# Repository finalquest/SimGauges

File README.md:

# SimGauges
XSIM simulator gauges control. Arduino PCB and arduino Code

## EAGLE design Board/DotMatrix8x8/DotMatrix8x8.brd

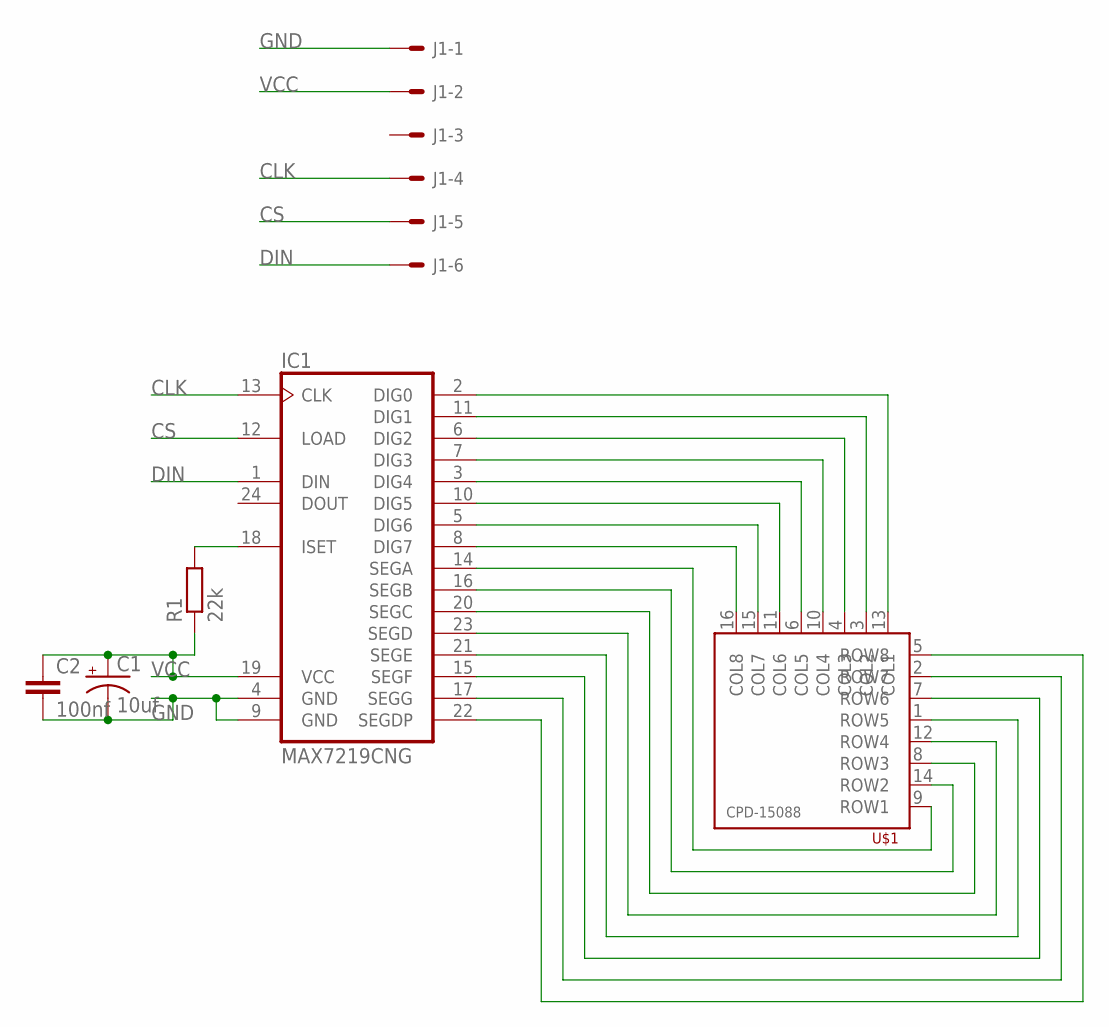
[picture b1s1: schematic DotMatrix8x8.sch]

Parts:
C1: 10uf; E2,5-6
C2: 100nf; C025-025X050
IC1: MAX7219CNG; DIL24-3
J1: 22-27-2061-06; 6410-06
R1: 22k; 0207/10
U$1: CPD-15088YGD2/A; CPD15088

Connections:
CLK: IC1.13 (CLK), J1.4
CS: IC1.12 (LOAD), J1.5
DIN: IC1.1 (DIN), J1.6
GND: C1.-, C2.2, IC1.4 (GND), IC1.9 (GND), J1.1
unnamed: IC1.18 (ISET), R1.2
unnamed: IC1.2 (DIG0), U$1.13 (COL1)
unnamed: IC1.11 (DIG1), U$1.3 (COL2)
unnamed: IC1.6 (DIG2), U$1.4 (COL3)
unnamed: IC1.7 (DIG3), U$1.10 (COL4)
unnamed: IC1.3 (DIG4), U$1.6 (COL5)
unnamed: IC1.10 (DIG5), U$1.11 (COL6)
unnamed: IC1.5 (DIG6), U$1.15 (COL7)
unnamed: IC1.8 (DIG7), U$1.16 (COL8)
unnamed: IC1.14 (SEGA), U$1.9 (ROW1)
unnamed: IC1.16 (SEGB), U$1.14 (ROW2)
unnamed: IC1.20 (SEGC), U$1.8 (ROW3)
unnamed: IC1.23 (SEGD), U$1.12 (ROW4)
unnamed: IC1.21 (SEGE), U$1.1 (ROW5)
unnamed: IC1.15 (SEGF), U$1.7 (ROW6)
unnamed: IC1.17 (SEGG), U$1.2 (ROW7)
unnamed: IC1.22 (SEGDP), U$1.5 (ROW8)
VCC: C1.+, C2.1, IC1.19 (VCC), J1.2, R1.1

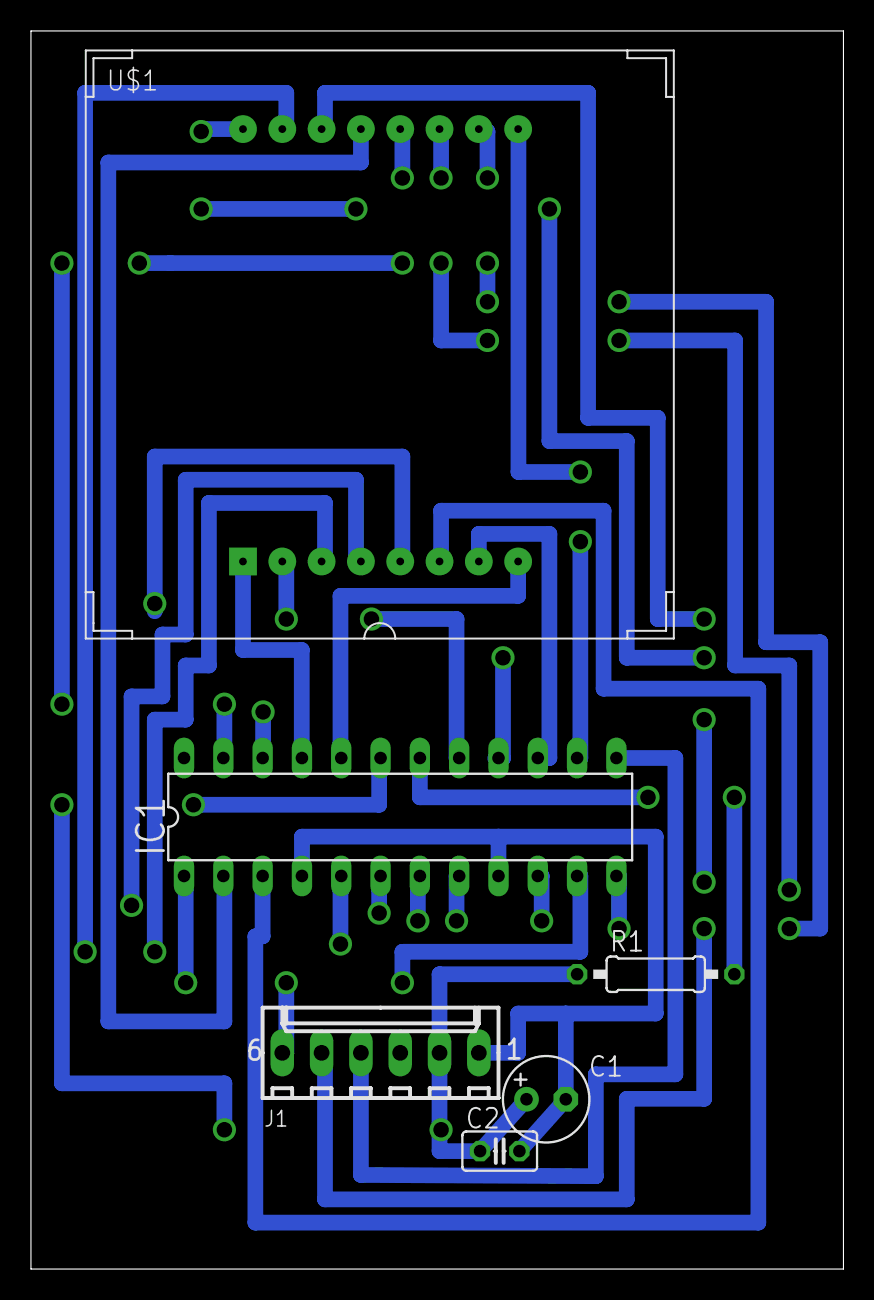
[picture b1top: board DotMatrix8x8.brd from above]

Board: 2 copper layers, 52.5 x 80.0 mm, 6 parts (0 on the bottom side), 22 nets.

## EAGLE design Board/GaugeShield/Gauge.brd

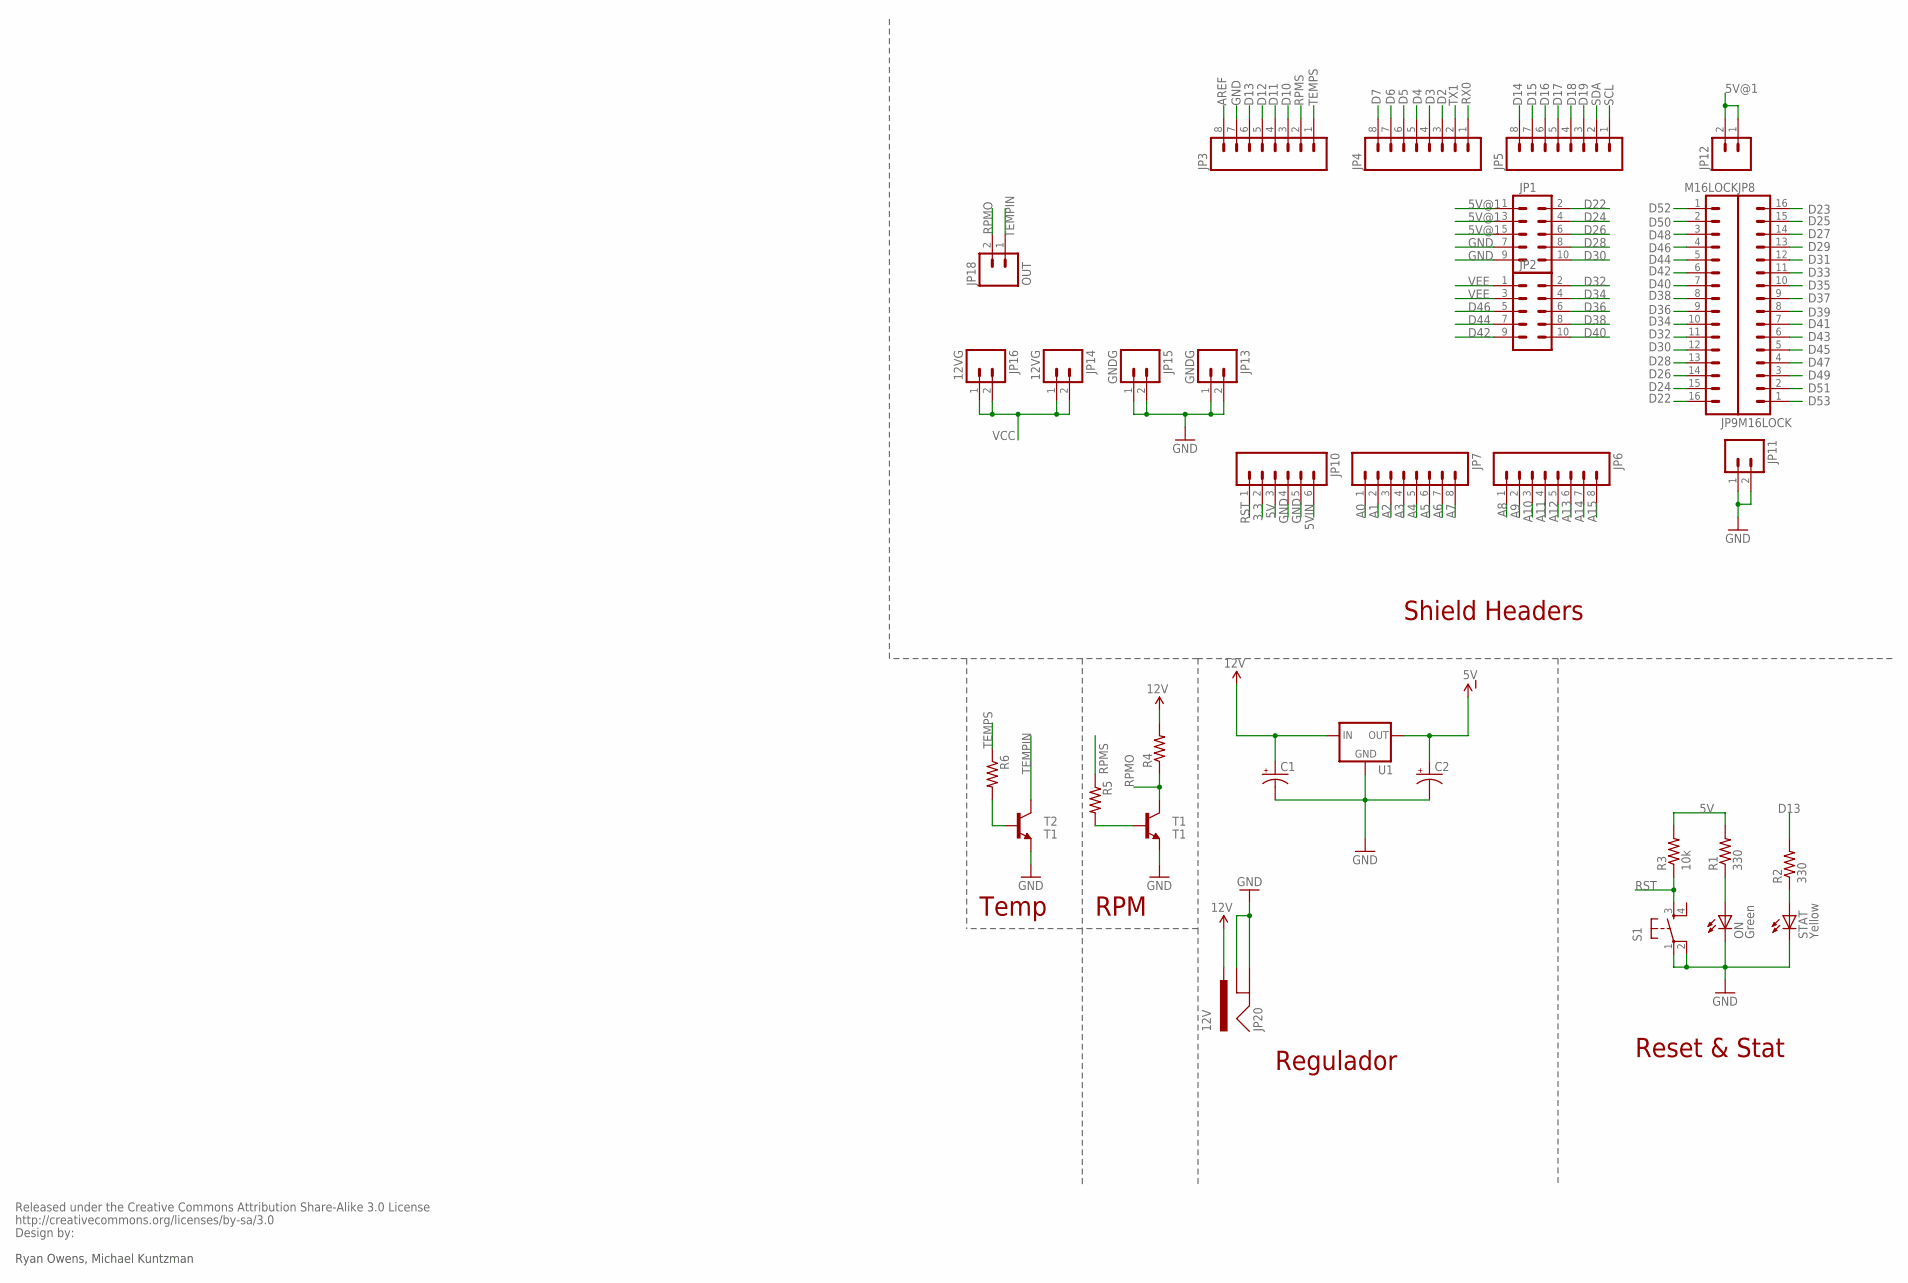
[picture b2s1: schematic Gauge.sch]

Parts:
C1, C2: 100UF-25V-20%(PTH); CPOL-RADIAL-100UF-25V
JP1, JP2: M05X2PTH; AVR_ICSP
JP3, JP4, JP5, JP6, JP7: M08LOCK; 1X08_LOCK
JP8, JP9: M16LOCK; 1X16_LOCK
JP10: M06LOCK; 1X06_LOCK
JP11, JP12: M02LOCK; 1X02_LOCK
JP13, JP15: GNDG; MOLEX-1X2
JP14, JP16: 12VG; MOLEX-1X2
JP18: OUT; MOLEX-1X2
JP20: 12V; POWER_JACK_PTH_LOCK
ON: Green; LED-0603
R1, R2: 330; 0603-RES
R3: 10k; 0603-RES
R4, R5, R6: RESISTORPTH-1/2W; AXIAL-0.5
S1: TAC_SWITCHSMD; TACTILE_SWITCH_SMD
STAT: Yellow; LED-0603
T1, T2: T1; TO-92
U1: V_REG_78XX-TO-220; TO-220-ALT
U$2: CREATIVE_COMMONS

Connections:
3.3: JP10.2
5V: JP10.3, R1.2, R3.2
5V@1: JP1.1, JP1.3, JP1.5, JP12.1, JP12.2
5VIN: C2.1 (+), JP10.6, U1.OUT
A0: JP7.1
A1: JP7.2
A2: JP7.3
A3: JP7.4
A4: JP7.5
A5: JP7.6
A6: JP7.7
A7: JP7.8
A8: JP6.1
A9: JP6.2
A10: JP6.3
A11: JP6.4
A12: JP6.5
A13: JP6.6
A14: JP6.7
A15: JP6.8
AREF: JP3.8
D2: JP4.3
D3: JP4.4
D4: JP4.5
D5: JP4.6
D6: JP4.7
D7: JP4.8
D10: JP3.3
D11: JP3.4
D12: JP3.5
D13: JP3.6, R2.2
D14: JP5.8
D15: JP5.7
D16: JP5.6
D17: JP5.5
D18: JP5.4
D19: JP5.3
D22: JP1.2, JP9.16
D23: JP8.16
D24: JP1.4, JP9.15
D25: JP8.15
D26: JP1.6, JP9.14
D27: JP8.14
D28: JP1.8, JP9.13
D29: JP8.13
D30: JP1.10, JP9.12
D31: JP8.12
D32: JP2.2, JP9.11
D33: JP8.11
D34: JP2.4, JP9.10
D35: JP8.10
D36: JP2.6, JP9.9
D37: JP8.9
D38: JP2.8, JP9.8
D39: JP8.8
D40: JP2.10, JP9.7
D41: JP8.7
D42: JP2.9, JP9.6
D43: JP8.6
D44: JP2.7, JP9.5
D45: JP8.5
D46: JP2.5, JP9.4
D47: JP8.4
D48: JP9.3
D49: JP8.3
D50: JP9.2
D51: JP8.2
D52: JP9.1
D53: JP8.1
GND: C1.2 (-), C2.2 (-), JP1.7, JP1.9, JP3.7, JP10.4, JP10.5, JP11.1, JP11.2, JP13.1, JP13.2, JP15.1, JP15.2, JP20.GND, JP20.GNDBREAK, ON.C, S1.1, S1.2, STAT.C, T1.3 (E), T2.3 (E), U1.GND
unnamed: R5.P$2 (2), T1.2 (B)
unnamed: R6.P$2 (2), T2.2 (B)
unnamed: ON.A, R1.1
unnamed: R2.1, STAT.A
RPMO: JP18.2, R4.P$1 (1), T1.1 (C)
RPMS: JP3.2, R5.P$1 (1)
RST: JP10.1, R3.1, S1.3
RX0: JP4.1
SCL: JP5.1
SDA: JP5.2
TEMPIN: JP18.1, T2.1 (C)
TEMPS: JP3.1, R6.P$1 (1)
TX1: JP4.2
VCC: C1.1 (+), JP14.1, JP14.2, JP16.1, JP16.2, JP20.PWR, U1.IN
VEE: JP2.1, JP2.3
VNEG: R4.P$2 (2)

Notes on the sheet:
Ryan Owens, Michael Kuntzman
Shield Headers
Reset & Stat
Regulador
RPM
Temp

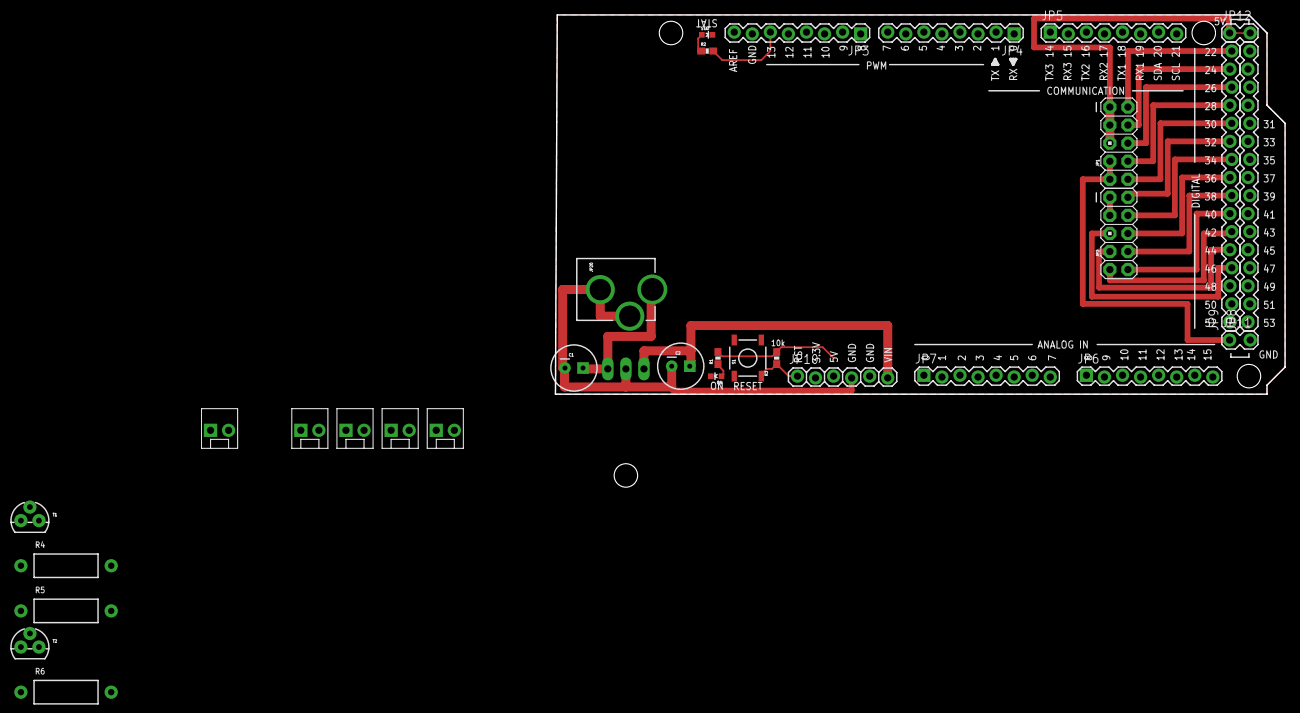
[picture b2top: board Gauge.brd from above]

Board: 2 copper layers, 102.6 x 53.3 mm, 36 parts (1 on the bottom side), 29 nets.

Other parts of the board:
U$3, U$4, U$5: STAND-OFF

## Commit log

2015-12-16 Subo el esquematico del board y el codigo para control de temp rpm y shift
2015-12-17 empece a diagramar la parte del board y a tracear las rutas
2016-01-01 placa para display 7seg hecha con leds, sin modulo de control
2016-01-01 7segmentos hecho con led, pero con la controladora incluida
2016-01-09 removed lock files
2016-01-10 Matriz 8x8 anodo comun

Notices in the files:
parts and their libraries:
SparkFun: Released under the Creative Commons Attribution Share-Alike 3.0 License
SparkFun: http://creativecommons.org/licenses/by-sa/3.0
SparkFun-Connectors: Licensing: Creative Commons ShareAlike 4.0 International - https://creativecommons.org/licenses/by-sa/4.0
